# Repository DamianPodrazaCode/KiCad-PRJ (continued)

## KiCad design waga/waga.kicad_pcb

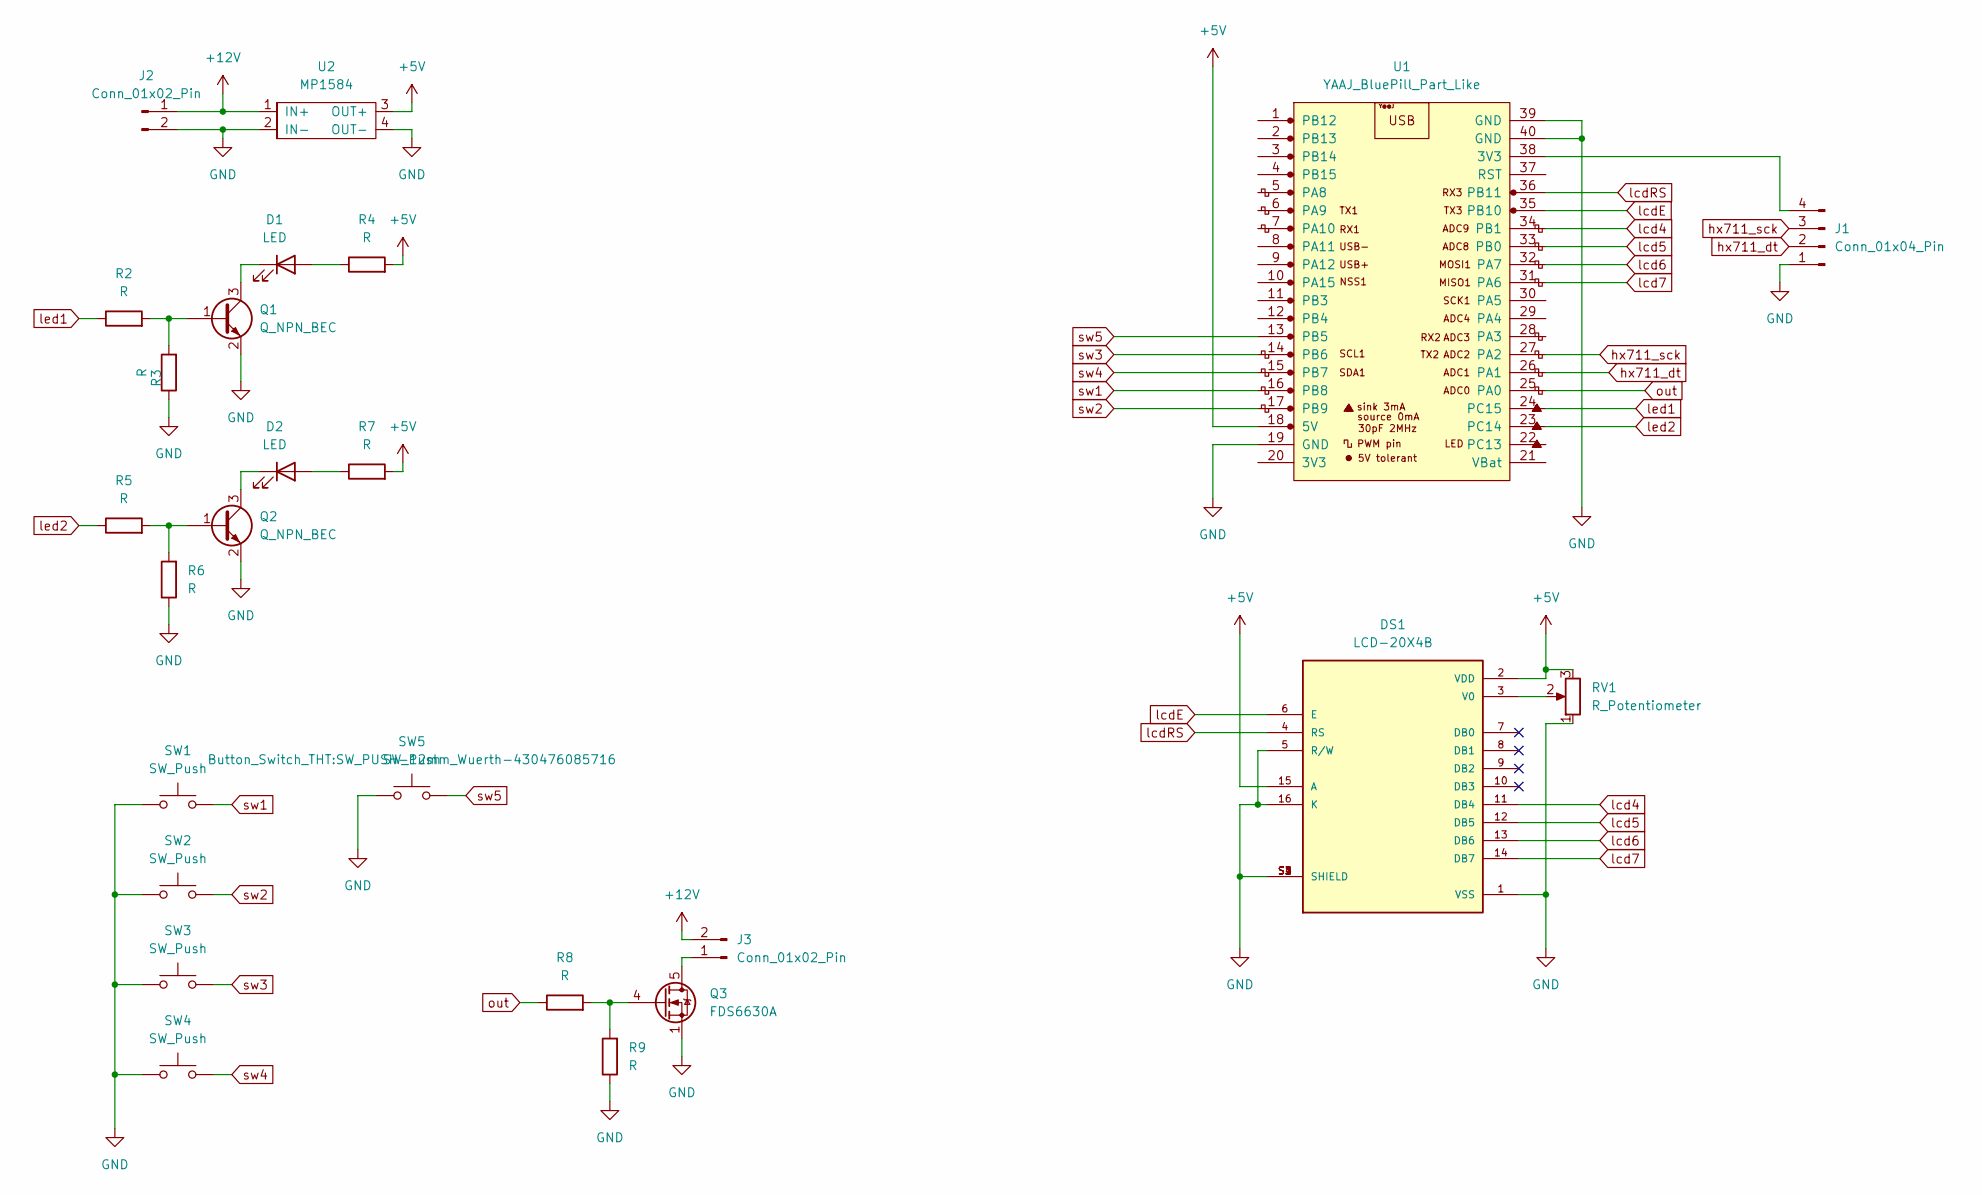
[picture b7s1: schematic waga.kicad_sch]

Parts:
D1, D2: LED; LED_D5.0mm
DS1: LCD-20X4B; LCD_LCD-20X4B
J1: Conn_01x04_Pin; PinHeader_1x04_P2.54mm_Vertical
J2, J3: Conn_01x02_Pin; PhoenixContact_MSTBVA_2,5_2-G_1x02_P5.00mm_Vertical
Q1, Q2: Q_NPN_BEC; SOT-23-3
Q3: FDS6630A; SOIC-8_3.9x4.9mm_P1.27mm
R2, R3, R4, R5, R6, R7, R8, R9: R; R_1206_3216Metric_Pad1.30x1.75mm_HandSolder
RV1: R_Potentiometer; Potentiometer_Vishay_T93YA_Vertical
SW1, SW2, SW3, SW4: SW_Push; SW_PUSH_6mm_H5mm
SW5: SW_Push; SW_PUSH-12mm_Wuerth-430476085716
U1: YAAJ_BluePill_Part_Like; YAAJ_BluePill_2
U2: MP1584

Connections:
+5V: DS1.2 (VDD), DS1.15 (A), R4.2, R7.2, RV1.3, U1.18 (5V), U2.3 (OUT+)
+12V: J2.1, J3.2, U2.1 (IN+)
GND: DS1.1 (VSS), DS1.5 (R/W), DS1.16 (K), DS1.S1 (SHIELD), DS1.S2 (SHIELD), DS1.S3 (SHIELD), DS1.S4 (SHIELD), J1.1, J2.2, Q1.2 (E), Q2.2 (E), Q3.1 (S), Q3.2 (S), Q3.3 (S), R3.1, R6.1, R9.1, RV1.1, SW1.1, SW2.1, SW3.1, SW4.1, SW5.1, U1.19 (GND), U1.39 (GND), U1.40 (GND), U2.2 (IN-), U2.4 (OUT-)
unnamed: D1.2 (A), R4.1
unnamed: D1.1 (K), Q1.3 (C)
unnamed: D2.2 (A), R7.1
unnamed: D2.1 (K), Q2.3 (C)
unnamed: DS1.3 (V0), RV1.2
unnamed: J1.4, U1.38 (3V3)
unnamed: J3.1, Q3.5 (D), Q3.6 (D), Q3.7 (D), Q3.8 (D)
unnamed: Q1.1 (B), R2.2, R3.2
unnamed: Q2.1 (B), R5.2, R6.2
unnamed: Q3.4 (G), R8.2, R9.2
hx711_dt: J1.2, U1.26 (PA1)
hx711_sck: J1.3, U1.27 (PA2)
lcd4: DS1.11 (DB4), U1.34 (PB1)
lcd5: DS1.12 (DB5), U1.33 (PB0)
lcd6: DS1.13 (DB6), U1.32 (PA7)
lcd7: DS1.14 (DB7), U1.31 (PA6)
lcdE: DS1.6 (E), U1.35 (PB10)
lcdRS: DS1.4 (RS), U1.36 (PB11)
led1: R2.1, U1.24 (PC15)
led2: R5.1, U1.23 (PC14)
out: R8.1, U1.25 (PA0)
sw1: SW1.2, U1.16 (PB8)
sw2: SW2.2, U1.17 (PB9)
sw3: SW3.2, U1.14 (PB6)
sw4: SW4.2, U1.15 (PB7)
sw5: SW5.2, U1.13 (PB5)

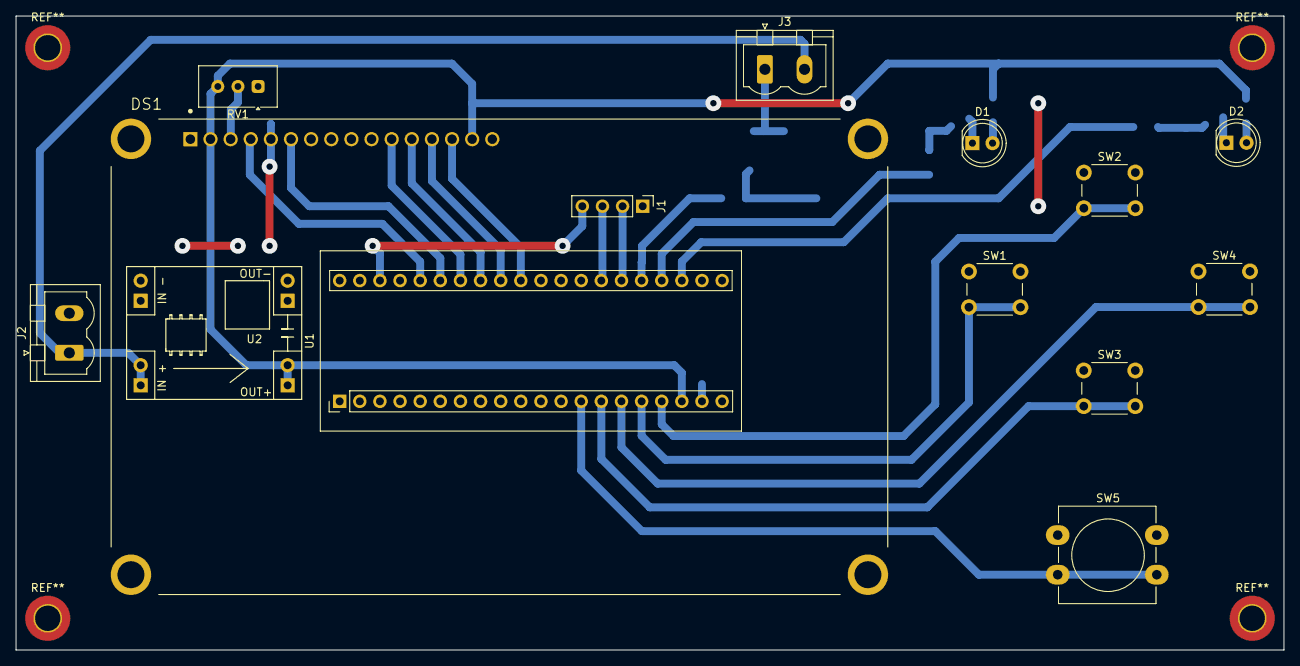
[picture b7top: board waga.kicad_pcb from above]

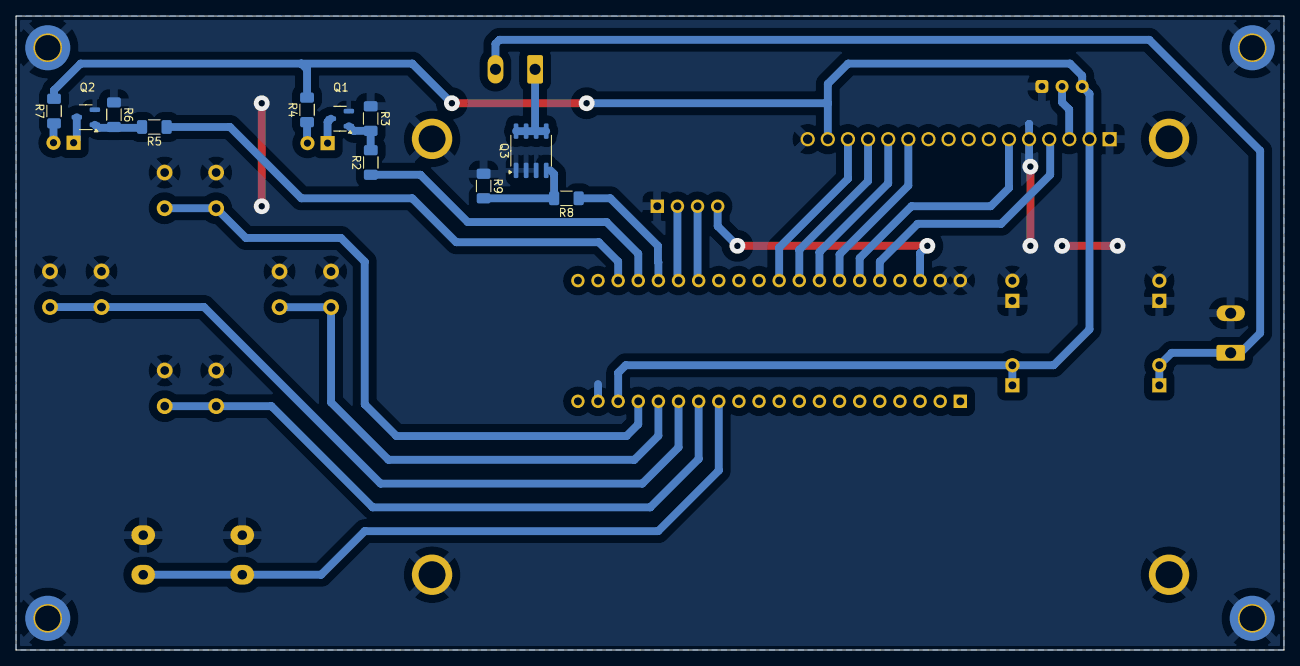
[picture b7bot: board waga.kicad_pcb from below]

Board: 2 copper layers, 160.0 x 80.0 mm, 25 parts (11 on the bottom side), 29 nets.

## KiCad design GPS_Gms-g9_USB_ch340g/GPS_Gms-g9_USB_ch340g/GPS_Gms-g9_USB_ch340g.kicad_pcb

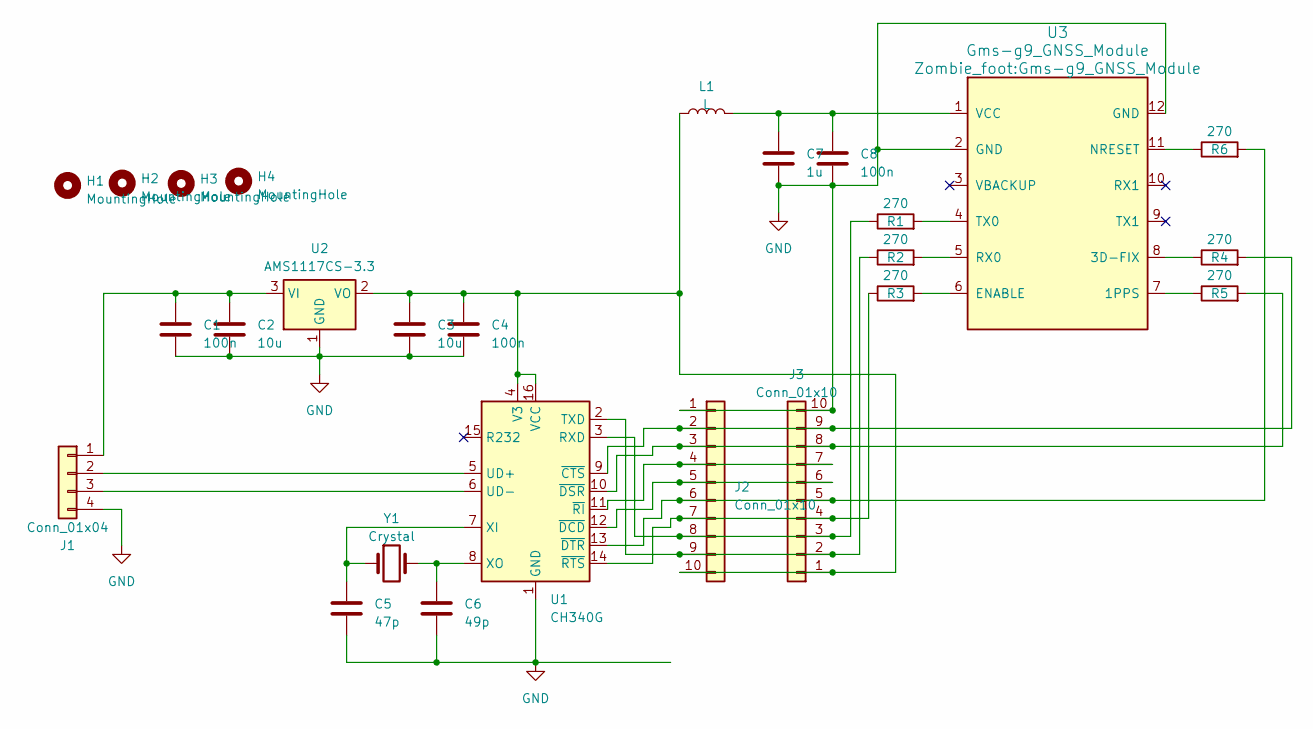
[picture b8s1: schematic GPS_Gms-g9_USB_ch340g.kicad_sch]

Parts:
C1, C4, C8: 100n; C_0805_2012Metric_Pad1.18x1.45mm_HandSolder
C2, C3: 10u; C_0805_2012Metric_Pad1.18x1.45mm_HandSolder
C5: 47p; C_0805_2012Metric_Pad1.18x1.45mm_HandSolder
C6: 49p; C_0805_2012Metric_Pad1.18x1.45mm_HandSolder
C7: 1u; C_0805_2012Metric_Pad1.18x1.45mm_HandSolder
H1, H2, H3, H4: MountingHole; MountingHole_3.2mm_M3
J1: Conn_01x04; PinHeader_1x04_P2.54mm_Vertical
J2, J3: Conn_01x10; PinHeader_1x10_P2.54mm_Vertical
L1: L; L_1206_3216Metric_Pad1.42x1.75mm_HandSolder
R1, R2, R3, R4, R5, R6: 270; R_0805_2012Metric_Pad1.20x1.40mm_HandSolder
U1: CH340G; SOIC-16_3.9x9.9mm_P1.27mm
U2: AMS1117CS-3.3; SOT-223-3_TabPin2
U3: Gms-g9_GNSS_Module
Y1: Crystal; Crystal_HC49-U_Vertical

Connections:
GND: C1.2, C2.2, C3.2, C4.2, C5.2, C6.2, C7.2, C8.2, J1.4, J2.1, J3.10, U1.1 (GND), U2.1 (GND), U3.2 (GND), U3.12 (GND)
unnamed: C1.1, C2.1, J1.1, U2.3 (VI)
unnamed: J1.2, U1.5 (UD+)
unnamed: J1.3, U1.6 (UD-)
unnamed: J2.2, J3.9, R4.2, U1.9 (~CTS)
unnamed: J2.3, J3.8, R5.2, U1.10 (~DSR)
unnamed: J2.4, J3.7, U1.11 (~RI)
unnamed: J2.5, J3.6, U1.12 (~DCD)
unnamed: J2.6, J3.5, R6.2, U1.13 (~DTR)
unnamed: J2.7, J3.4, R3.1, U1.14 (~RTS)
unnamed: J2.8, J3.3, R1.1, U1.3 (RXD)
unnamed: J2.9, J3.2, R2.1, U1.2 (TXD)
unnamed: C3.1, C4.1, J2.10, J3.1, L1.1, U1.4 (V3), U1.16 (VCC), U2.2 (VO)
unnamed: C5.1, U1.7 (XI), Y1.1
unnamed: C6.1, U1.8 (XO), Y1.2
unnamed: R5.1, U3.7 (1PPS)
unnamed: R4.1, U3.8 (3D-FIX)
unnamed: R3.2, U3.6 (ENABLE)
unnamed: R6.1, U3.11 (NRESET)
unnamed: R2.2, U3.5 (RX0)
unnamed: R1.2, U3.4 (TX0)
unnamed: C7.1, C8.1, L1.2, U3.1 (VCC)

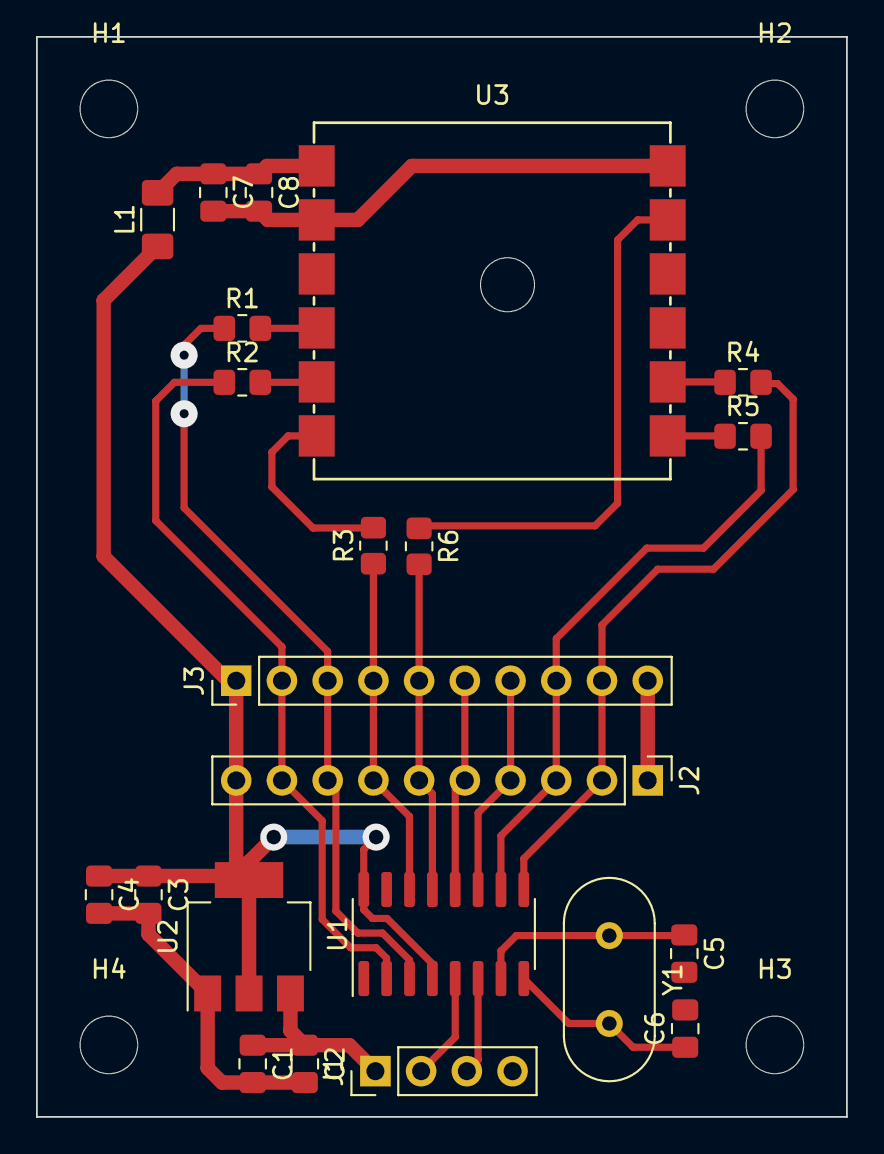
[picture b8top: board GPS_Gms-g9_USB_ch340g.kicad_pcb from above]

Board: 2 copper layers, 45.0 x 60.0 mm, 26 parts (0 on the bottom side), 22 nets.

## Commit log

2024-10-06 Update esp32_IMU_GPS-Dolna sygnałowa.dxf, esp32_IMU_GPS-Krawędziowa.dxf, esp32_IMU_GPS.kicad_pcb, and 131 more files
2026-01-22 Add KiCad project files and symbol library
    Initial import of KiCad project files, including schematic, PCB layout, project settings, symbol library, and backup archives for the PID_KLIMA project.
